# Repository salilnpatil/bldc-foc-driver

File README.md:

# BLDC Field-Oriented Control Driver

A custom three-phase inverter board and closed-loop firmware for driving a brushless DC (BLDC) motor using **Field-Oriented Control (FOC)**. Developed as my final-year B.Tech thesis and deployed as the pitch-axis actuator of a gimbal demonstrator: an external RC-style PWM signal commands a target angle, and the motor tracks it smoothly through a 3:1 gear reduction.

## Stack at a glance

| Layer | Choice |
| --- | --- |
| MCU | STM32G431 (Cortex-M4F + CORDIC coprocessor) |
| Commutation | 6-PWM, voltage-mode FOC ([SimpleFOC](https://simplefoc.com/)) |
| Position sensor | MA730 14-bit magnetic encoder (SPI) |
| Power stage | 3× half-bridge, TI N-channel MOSFETs |
| Setpoint input | RC-style PWM (timer input capture) |
| PCB tool | Autodesk EagleCAD |
| Bus voltage | 12 V (nominal) |

## Visuals

| PCB layout | Wiring diagram |
| --- | --- |
|  |  |

Communication interface:

## Repository layout

```
.
├── Assets/                              Demo GIF, connection diagrams, PCB render, final paper
├── Hardware_assets/
│   ├── Design_FIle(EagleCad)/           EagleCAD .brd + .sch sources
│   ├── Schematic/                       Exported PDF schematic
│   ├── Gerber_file/                     Fabrication-ready Gerbers (.zip)
│   └── BOM_&_Component_selection/       MOSFET trade-off spreadsheet
├── Firmware/
│   └── bldc-doc-driver/                 Arduino sketch (SimpleFOC on STM32G4)
└── README.md
```

## Hardware design

The board is a three-phase inverter built around three half-bridges of TI N-channel power MOSFETs, with an MA730 magnetic encoder front-end and a PWM-input pin exposed to an off-board receiver. A mechanical limit switch on the pitch axis provides a repeatable zero for homing.

**MOSFET selection** — the workbook in `Hardware_assets/BOM_&_Component_selection/` compares two TI candidates evaluated for the low-side/high-side switches:

| Part | Vds | Id | Rds(on) max | Qg | Notes |
| --- | --- | --- | --- | --- | --- |
| `CSD18510Q5B` | 40 V | 42 A | 1.2 mΩ | 118 nC | Lower Qgd, lower voltage headroom |
| `CSD18536KCS` | 60 V | 200 A | 1.3 mΩ | 108 nC | Higher Vds margin, much higher current rating |

Both sit at roughly 1.2–1.3 mΩ Rds(on), so the choice comes down to voltage headroom above the 12 V bus and thermal budget rather than conduction loss.

**Design artefacts**

- EagleCAD sources — [`Hardware_assets/Design_FIle(EagleCad)/Layout_Design_File.sch`](Hardware_assets/Design_FIle(EagleCad)/Layout_Design_File.sch), [`Schematic_Design_File.brd`](Hardware_assets/Design_FIle(EagleCad)/Schematic_Design_File.brd)
- Schematic PDF — [`Hardware_assets/Schematic/Final_Schematic.pdf`](Hardware_assets/Schematic/Final_Schematic.pdf)
- Gerbers — [`Hardware_assets/Gerber_file/Final_Gerber_File.zip`](Hardware_assets/Gerber_file/Final_Gerber_File.zip)

## Firmware

Sketch: [`Firmware/bldc-doc-driver/bldc-doc-driver.ino`](Firmware/bldc-doc-driver/bldc-doc-driver.ino).

**Control law** — SimpleFOC angle-control cascade: `angle (P) → velocity (PI) → q-axis voltage`. Torque mode is `TorqueControlType::voltage`, pole pairs are set to 7, and the motor voltage limit is clamped to `V_PSU / 2` for headroom.

**Parameters** (from the sketch)

| Define / field | Value |
| --- | --- |
| `V_PSU`, `V_LIMIT` | 12.0 V |
| `GEAR_REDUCTION` | 3 (pitch axis) |
| `ACCESSIBLE_ANGLE` | 3.00 rad of mechanical pitch travel |
| `PWM_IN_MIN` / `PWM_IN_MAX` | 4.94 % / 10.06 % duty (≈1.0–2.0 ms pulses) |
| `PID_velocity` P / I / D | 0.2 / 4 / 0 |
| `P_angle.P` | 10 |
| `velocity_limit` | 50 rad/s |

**Startup sequence**

1. Bring up the debug serial (`Serial3`, 115200), the STM32G4 CORDIC unit, the PWM input capture, and the MA730 sensor.
2. Configure driver + motor, run SimpleFOC `initFOC()` electrical alignment.
3. **Homing** — drive the motor slowly toward the limit switch; when it trips, snapshot the encoder angle as `max_angle`, compute `min_angle = max_angle − (ACCESSIBLE_ANGLE × GEAR_REDUCTION)`.
4. Build a linear mapper from input PWM duty `[4.94 %, 10.06 %]` onto `[min_angle, max_angle]`.

**Main loop** — `motor.loopFOC()` runs the current/voltage inner loop; each iteration the PWM-input duty is sampled, mapped to a target angle, clamped to the calibrated travel, and passed to `motor.move(target_angle)`.

### Library dependencies

- [SimpleFOC](https://github.com/simplefoc/Arduino-FOC) — `BLDCMotor`, `BLDCDriver6PWM`
- [SimpleFOC Drivers](https://github.com/simplefoc/Arduino-FOC-drivers) — `MagneticSensorMA730`, `STM32PWMInput`, `STM32G4CORDICTrigFunctions`, `STM32FlashSettingsStorage`
- [Arduino core for STM32 (stm32duino)](https://github.com/stm32duino/Arduino_Core_STM32) — board target: **Generic STM32G4 series / STM32G431xx**

### Build & flash (Arduino IDE)

1. Install Arduino IDE 2.x and the **STM32** boards package following stm32duino's instructions.
2. From Library Manager, install `SimpleFOC` and `SimpleFOC Drivers`.
3. Open `Firmware/bldc-doc-driver/bldc-doc-driver.ino`.
4. Board → *Generic STM32G4 series*; part → *STM32G431xx*; upload method → *STM32CubeProgrammer (SWD)* via an ST-Link.
5. Compile and flash.

### Known gaps / roadmap

- **STM32CubeIDE port** — planned. A HAL/LL implementation in STM32CubeIDE (native 6-PWM timer configuration, ADC-based phase current sensing, CORDIC-accelerated Park/Clarke) is on the roadmap as a production-grade replacement for the Arduino prototype. Not yet in-tree.

## Research paper

Full write-up covering FOC theory, hardware design rationale, and results: [`Assets/Final_Paper.pdf`](Assets/Final_Paper.pdf).

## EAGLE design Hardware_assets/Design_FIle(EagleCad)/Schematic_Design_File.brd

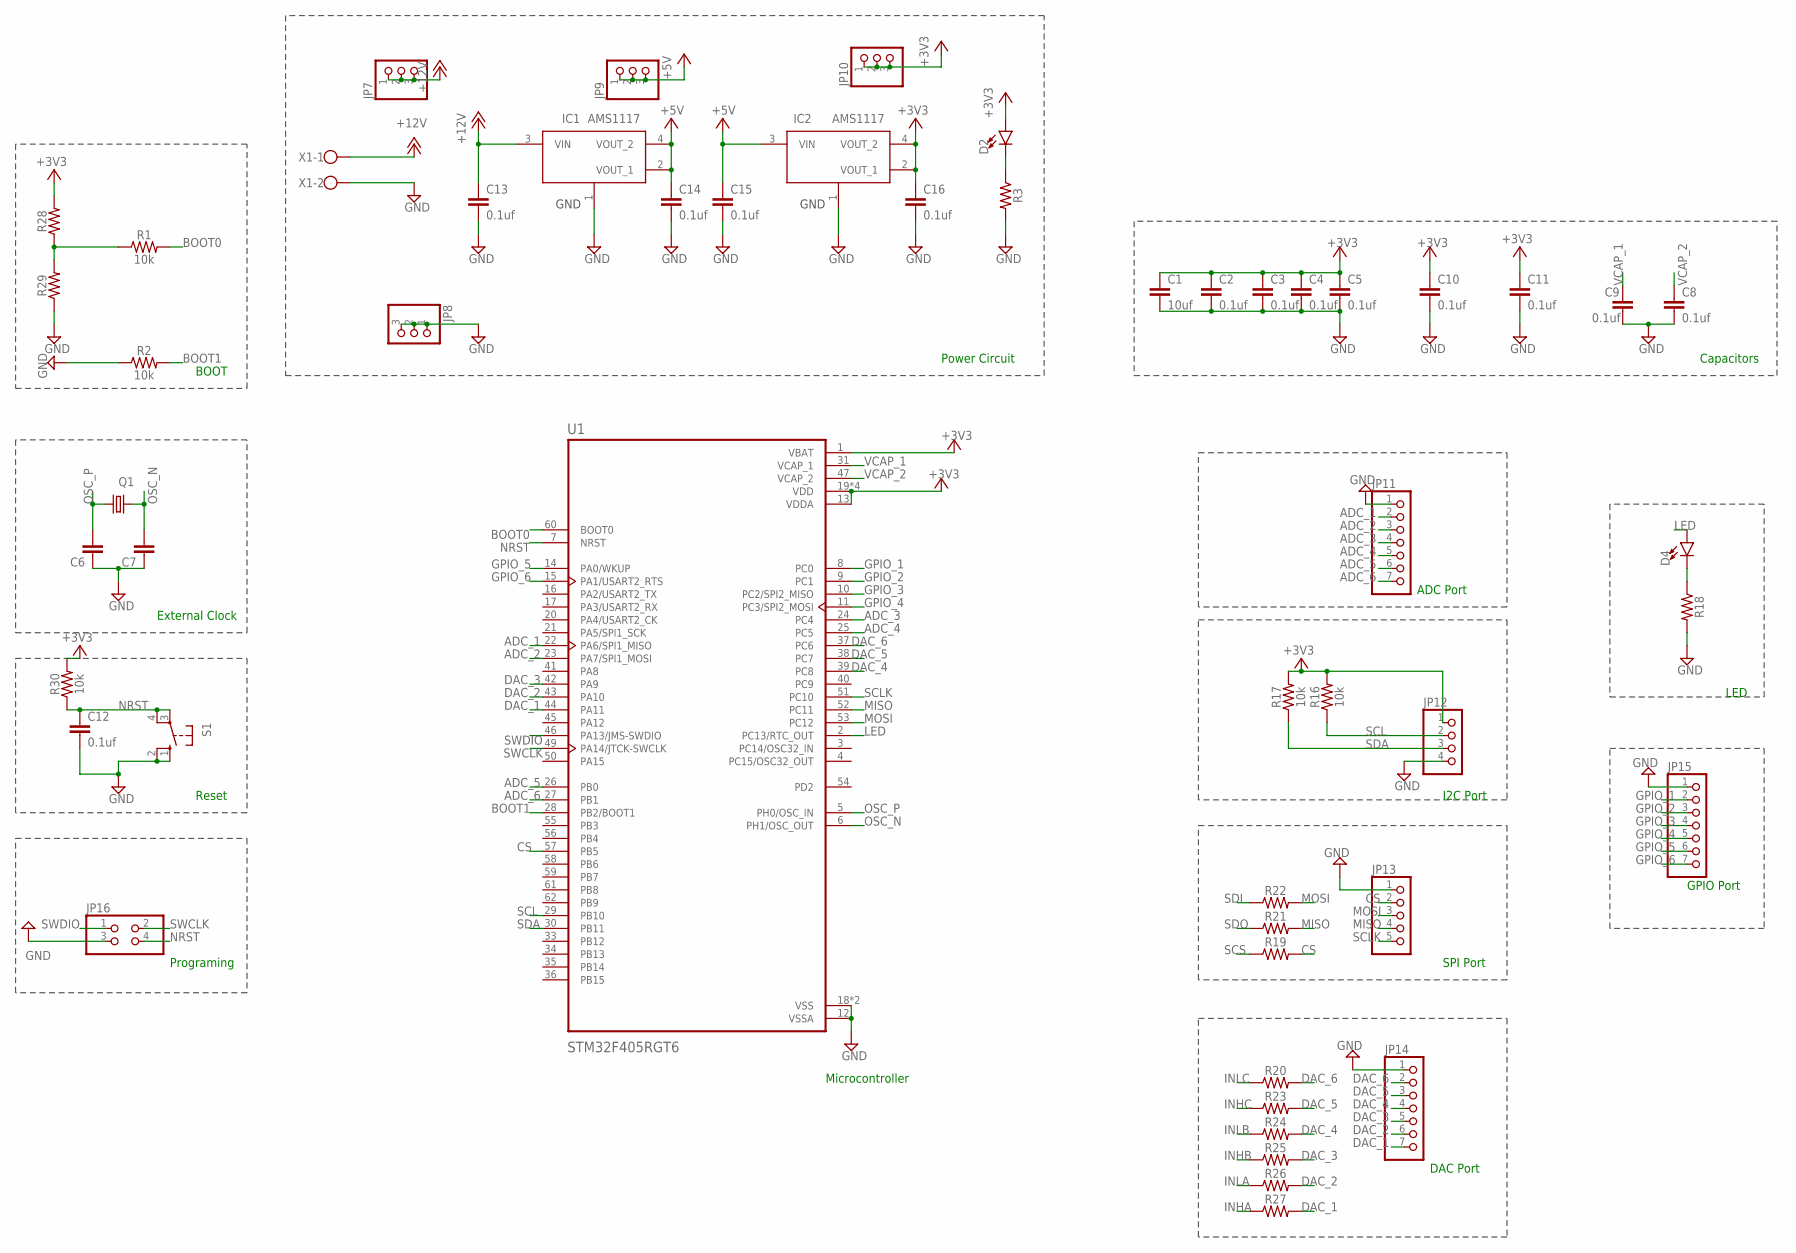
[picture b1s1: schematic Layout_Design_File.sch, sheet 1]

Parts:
C1: 10uf; 0603
C2, C3, C4, C5, C8, C9, C10, C11, C12, C13, C14, C15, C16: 0.1uf; 0603
C6, C7: CAP-0603; 0603
D2, D4: LED1206; LED-1206
IC1, IC2: AMS1117; SOT229P700X180-4N
JP7, JP8, JP9, JP10: PINHD-1X3; 1X03
JP11, JP14, JP15: PINHD-1X7; 1X07
JP12: PINHD-1X4; 1X04
JP13: PINHD-1X5; 1X05
JP16: PINHD-2X2; 2X02
Q1: CRYSTALHC49S; HC49/S
R1, R2, R16, R17, R30: 10k; 0603
R3, R18, R19, R20, R21, R22, R23, R24, R25, R26, R27, R28, R29: 0603
S1: 10-XX; B3F-10XX
U1: STM32F405RGT6; QFP50P1200X1200X160-64N
X1: W237-102

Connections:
+3V3: C1.1, C2.1, C3.1, C4.1, C5.1, C10.1, C11.1, C16.1, D2.A, IC2.2 (VOUT_1), IC2.4 (VOUT_2), JP10.1, JP10.2, JP10.3, JP12.1, R16.2, R17.2, R28.2, R30.2, U1.1 (VBAT), U1.13 (VDDA), U1.19 (VDD), U1.32 (VDD), U1.48 (VDD), U1.64 (VDD); also elsewhere on the board
+5V: C14.1, C15.1, IC1.2 (VOUT_1), IC1.4 (VOUT_2), IC2.3 (VIN), JP9.1, JP9.2, JP9.3
+12V: C13.1, IC1.3 (VIN), JP7.1, JP7.2, JP7.3, X1.1; also elsewhere on the board
ADC_1: JP11.2, U1.22 (PA6/SPI1_MISO)
ADC_2: JP11.3, U1.23 (PA7/SPI1_MOSI)
ADC_3: JP11.4, U1.24 (PC4)
ADC_4: JP11.5, U1.25 (PC5)
ADC_5: JP11.6, U1.26 (PB0)
ADC_6: JP11.7, U1.27 (PB1)
BOOT0: R1.2, U1.60 (BOOT0)
BOOT1: R2.2, U1.28 (PB2/BOOT1)
CS: JP13.2, R19.2, U1.57 (PB5)
DAC_1: JP14.7, R27.2, U1.44 (PA11)
DAC_2: JP14.6, R26.2, U1.43 (PA10)
DAC_3: JP14.5, R25.2, U1.42 (PA9)
DAC_4: JP14.4, R24.2, U1.39 (PC8)
DAC_5: JP14.3, R23.2, U1.38 (PC7)
DAC_6: JP14.2, R20.2, U1.37 (PC6)
GND: C1.2, C2.2, C3.2, C4.2, C5.2, C6.1, C7.1, C8.2, C9.2, C10.2, C11.2, C12.2, C13.2, C14.2, C15.2, C16.2, IC1.1 (GND), IC2.1 (GND), JP8.1, JP8.2, JP8.3, JP11.1, JP12.4, JP13.1, JP14.1, JP15.1, JP16.3, R2.1, R3.2, R18.2, R29.1, S1.1 (S), S1.2 (S1), U1.12 (VSSA), U1.18 (VSS), U1.63 (VSS), X1.2; also elsewhere on the board
GPIO_1: JP15.2, U1.8 (PC0)
GPIO_2: JP15.3, U1.9 (PC1)
GPIO_3: JP15.4, U1.10 (PC2/SPI2_MISO)
GPIO_4: JP15.5, U1.11 (PC3/SPI2_MOSI)
GPIO_5: JP15.6, U1.14 (PA0/WKUP)
GPIO_6: JP15.7, U1.15 (PA1/USART2_RTS)
INHA: R27.1; also elsewhere on the board
INHB: R25.1; also elsewhere on the board
INHC: R23.1; also elsewhere on the board
INLA: R26.1; also elsewhere on the board
INLB: R24.1; also elsewhere on the board
INLC: R20.1; also elsewhere on the board
LED: D4.A, U1.2 (PC13/RTC_OUT)
MISO: JP13.4, R21.2, U1.52 (PC11)
MOSI: JP13.3, R22.2, U1.53 (PC12)
unnamed: D2.C, R3.1
unnamed: D4.C, R18.1
unnamed: R1.1, R28.1, R29.2
NRST: C12.1, JP16.4, R30.1, S1.3, S1.4 (P1), U1.7 (NRST)
OSC_N: C7.2, Q1.2, U1.6 (PH1/OSC_OUT)
OSC_P: C6.2, Q1.1, U1.5 (PH0/OSC_IN)
SCL: JP12.2, R16.1, U1.29 (PB10)
SCLK: JP13.5, U1.51 (PC10); also elsewhere on the board
SCS: R19.1; also elsewhere on the board
SDA: JP12.3, R17.1, U1.30 (PB11)
SDI: R22.1; also elsewhere on the board
SDO: R21.1; also elsewhere on the board
SWCLK: JP16.2, U1.49 (PA14/JTCK-SWCLK)
SWDIO: JP16.1, U1.46 (PA13/JMS-SWDIO)
VCAP_1: C9.1, U1.31 (VCAP_1)
VCAP_2: C8.1, U1.47 (VCAP_2)

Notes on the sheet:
BOOT
External Clock
Reset
Programing
Power Circuit
Capacitors
Microcontroller
ADC Port
I2C Port
SPI Port
DAC Port
GPIO Port
LED

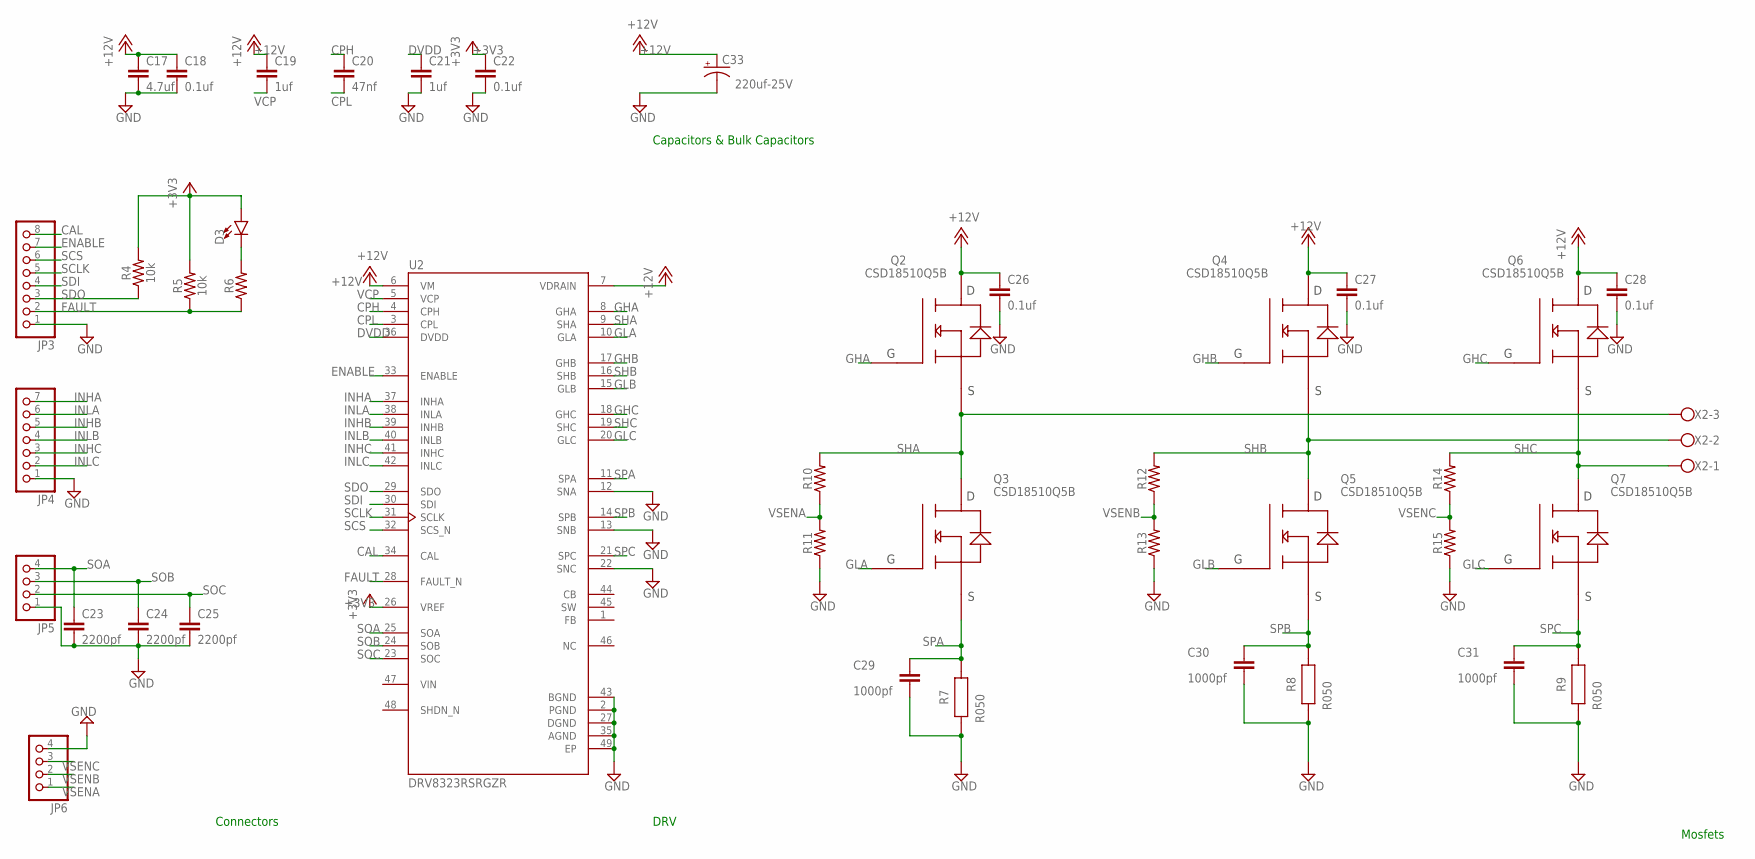
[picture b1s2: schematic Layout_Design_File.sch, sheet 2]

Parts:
C17: 4.7uf; 0603
C18, C22, C26, C27, C28: 0.1uf; 0603
C19, C21: 1uf; 0603
C20: 47nf; 0603
C23, C24, C25: 2200pf; 0603
C29, C30, C31: 1000pf; 0603
C33: 220uf-25V; CPOL-RADIAL-5MM-10MM-NS
D3: LED1206; LED-1206
JP3: PINHD-1X8; 1X08
JP4: PINHD-1X7; 1X07
JP5, JP6: PINHD-1X4; 1X04
Q2, Q3, Q4, Q5, Q6, Q7: CSD18510Q5B; CSD18540Q5BT
R4, R5: 10k; 0603
R6, R10, R11, R12, R13, R14, R15: 0603
R7, R8, R9: R050; WRIS_PSMC_2512_6.3X3.1X0.58X2.2(LXWXHXPW)
U2: DRV8323RSRGZR; QFN50P700X700X100-49N
X2: W237-103

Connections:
+3V3: C22.1, D3.A, R4.2, R5.2, U2.26 (VREF); also elsewhere on the board
+12V: C17.1, C18.1, C19.1, C26.1, C27.1, C28.1, C33.+, Q2.5 (D), Q2.6 (D), Q2.7 (D), Q2.8 (D), Q2.9 (D), Q4.5 (D), Q4.6 (D), Q4.7 (D), Q4.8 (D), Q4.9 (D), Q6.5 (D), Q6.6 (D), Q6.7 (D), Q6.8 (D), Q6.9 (D), U2.6 (VM), U2.7 (VDRAIN); also elsewhere on the board
CAL: JP3.8, U2.34 (CAL)
CB: U2.44 (CB)
CPH: C20.1, U2.4 (CPH)
CPL: C20.2, U2.3 (CPL)
DVDD: C21.1, U2.36 (DVDD)
ENABLE: JP3.7, U2.33 (ENABLE)
FAULT: JP3.2, R5.1, R6.1, U2.28 (FAULT_N)
GHA: Q2.4 (G), U2.8 (GHA)
GHB: Q4.4 (G), U2.17 (GHB)
GHC: Q6.4 (G), U2.18 (GHC)
GLA: Q3.4 (G), U2.10 (GLA)
GLB: Q5.4 (G), U2.15 (GLB)
GLC: Q7.4 (G), U2.20 (GLC)
GND: C17.2, C18.2, C21.2, C22.2, C23.2, C24.2, C25.2, C26.2, C27.2, C28.2, C29.2, C30.2, C31.2, C33.-, JP3.1, JP4.1, JP5.1, JP6.4, R7.1, R8.1, R9.1, R11.1, R13.1, R15.1, U2.2 (PGND), U2.12 (SNA), U2.13 (SNB), U2.22 (SNC), U2.27 (DGND), U2.35 (AGND), U2.43 (BGND), U2.49 (EP); also elsewhere on the board
INHA: JP4.7, U2.37 (INHA); also elsewhere on the board
INHB: JP4.5, U2.39 (INHB); also elsewhere on the board
INHC: JP4.3, U2.41 (INHC); also elsewhere on the board
INLA: JP4.6, U2.38 (INLA); also elsewhere on the board
INLB: JP4.4, U2.40 (INLB); also elsewhere on the board
INLC: JP4.2, U2.42 (INLC); also elsewhere on the board
unnamed: D3.C, R6.2
SCLK: JP3.5, U2.31 (SCLK); also elsewhere on the board
SCS: JP3.6, U2.32 (SCS_N); also elsewhere on the board
SDI: JP3.4, U2.30 (SDI); also elsewhere on the board
SDO: JP3.3, R4.1, U2.29 (SDO); also elsewhere on the board
SHA: Q2.1 (S), Q2.2 (S), Q2.3 (S), Q3.5 (D), Q3.6 (D), Q3.7 (D), Q3.8 (D), Q3.9 (D), R10.2, U2.9 (SHA), X2.3
SHB: Q4.1 (S), Q4.2 (S), Q4.3 (S), Q5.5 (D), Q5.6 (D), Q5.7 (D), Q5.8 (D), Q5.9 (D), R12.2, U2.16 (SHB), X2.2
SHC: Q6.1 (S), Q6.2 (S), Q6.3 (S), Q7.5 (D), Q7.6 (D), Q7.7 (D), Q7.8 (D), Q7.9 (D), R14.2, U2.19 (SHC), X2.1
SOA: C23.1, JP5.4, U2.25 (SOA)
SOB: C24.1, JP5.3, U2.24 (SOB)
SOC: C25.1, JP5.2, U2.23 (SOC)
SPA: C29.1, Q3.1 (S), Q3.2 (S), Q3.3 (S), R7.2, U2.11 (SPA)
SPB: C30.1, Q5.1 (S), Q5.2 (S), Q5.3 (S), R8.2, U2.14 (SPB)
SPC: C31.1, Q7.1 (S), Q7.2 (S), Q7.3 (S), R9.2, U2.21 (SPC)
VCP: C19.2, U2.5 (VCP)
VIN: U2.47 (VIN)
VSENA: JP6.1, R10.1, R11.2
VSENB: JP6.2, R12.1, R13.2
VSENC: JP6.3, R14.1, R15.2

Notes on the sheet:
Capacitors & Bulk Capacitors
Connectors
DRV
Mosfets

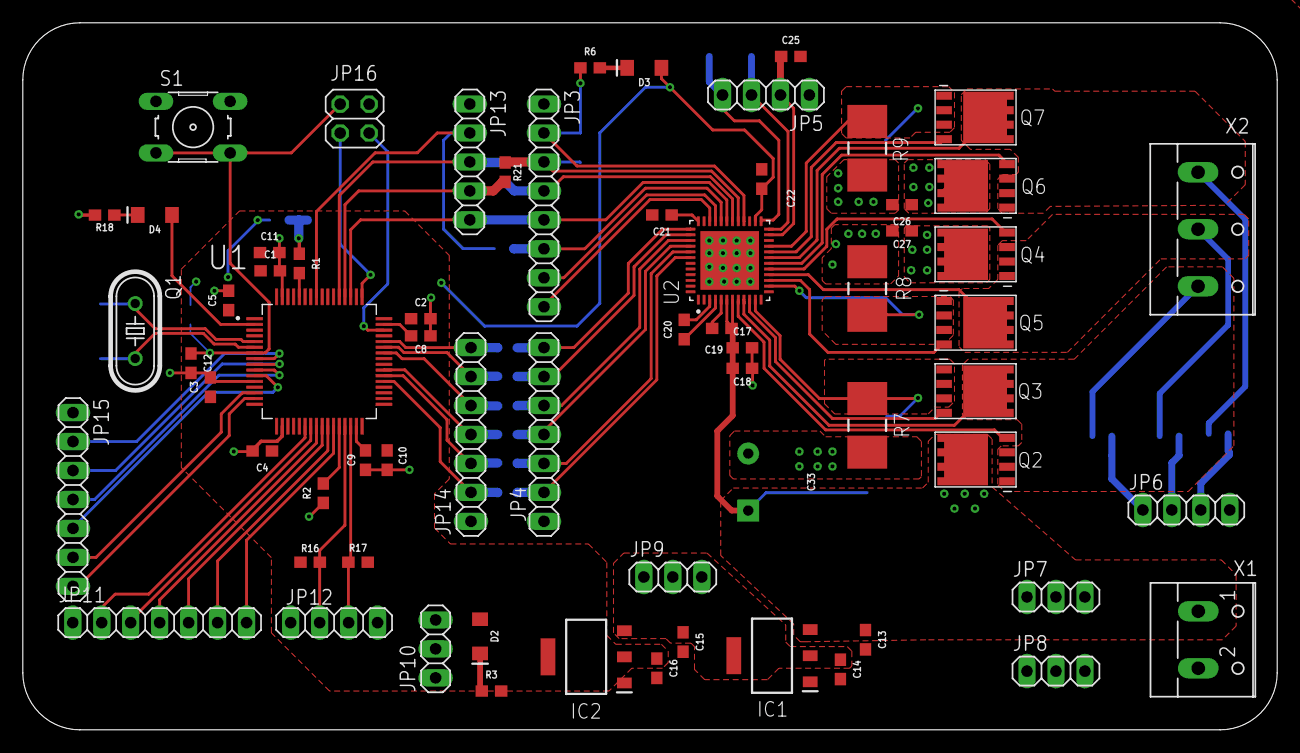
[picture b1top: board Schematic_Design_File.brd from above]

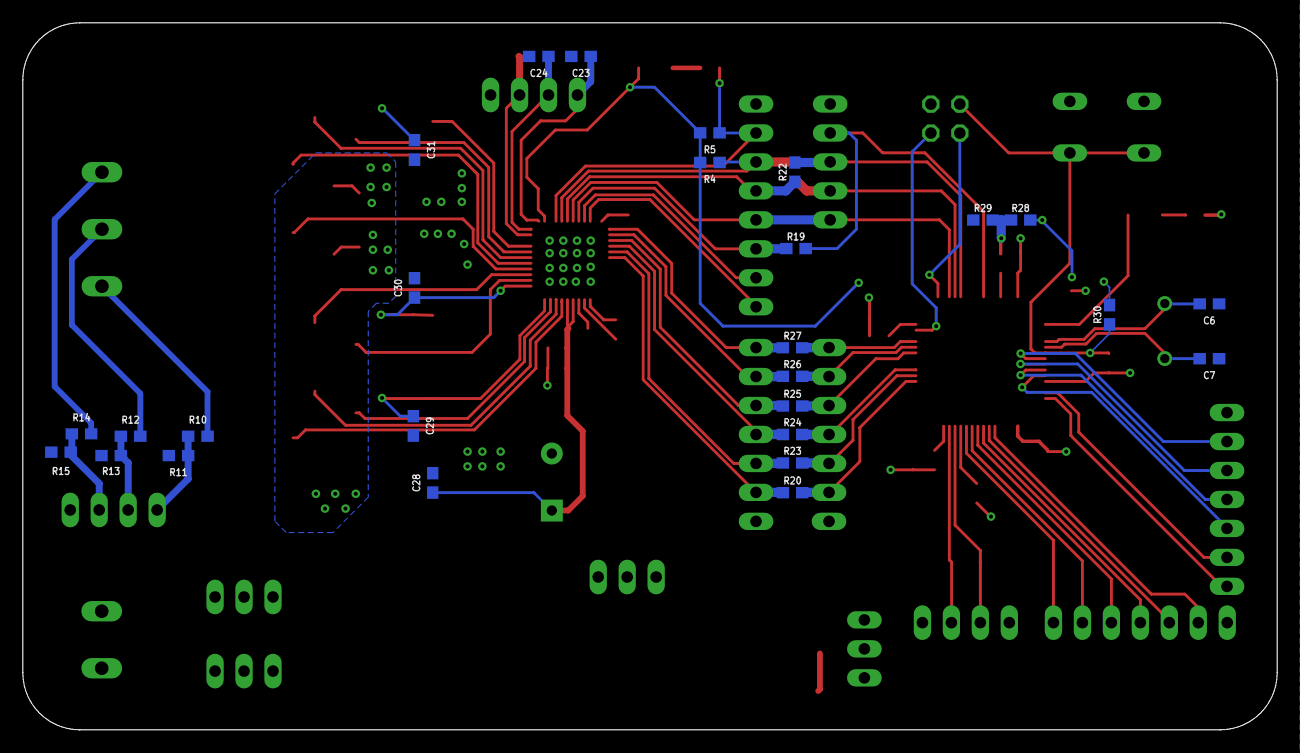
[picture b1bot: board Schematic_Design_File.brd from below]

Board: 2 copper layers, 110.0 x 62.0 mm, 93 parts (27 on the bottom side), 76 nets.

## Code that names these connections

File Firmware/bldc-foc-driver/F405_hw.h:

#ifndef F405_HW_H
#define F405_HW_H

/*
 * F405_hw.h — board pin map for the BLDC FOC driver board (STM32F405RGT6).
 *
 * Values are derived directly from the committed EagleCAD schematic at
 *   Hardware_assets/Design_FIle(EagleCad)/Layout_Design_File.sch
 *
 * Two categories of pins below:
 *
 *   HARDWIRED  — physically routed on the PCB from the MCU to the DRV8323
 *                gate driver through series resistors (R19..R27). These
 *                values are authoritative and should not be changed.
 *
 *   EXTERNAL   — the board brings the DRV8323 control pins (ENABLE, FAULT,
 *                CAL) out on JP3, and spare MCU GPIOs out on JP11..JP15.
 *                The connections from MCU GPIO to DRV-ENABLE, to the MA730
 *                encoder's chip-select, and to the limit switch / PWM
 *                input / debug UART are made off-board with jumper wires
 *                chosen at assembly time. The placeholders below are
 *                *suggested defaults* taken from pins broken out on JP15
 *                (GPIOs) and JP12 (UART-capable).
 *
 *                >>> VERIFY these match your physical jumper wiring before
 *                >>> flashing. A wrong ENABLE pin can leave the DRV8323 in
 *                >>> a permanently enabled state with no software control.
 *
 * Note: the parent sketch also calls into the STM32G4 hardware CORDIC,
 * which does not exist on the F4 family. Those calls must be removed for
 * the F405 target. This header only defines pins; it does not fix that.
 */

// ---------------------------------------------------------------------------
// HARDWIRED — 6-PWM gate-driver inputs to DRV8323RS (via R20/R23..R27)
// ---------------------------------------------------------------------------
// Phase A:  PA11 (R27) -> INHA,  PA10 (R26) -> INLA
// Phase B:  PA9  (R25) -> INHB,  PC8  (R24) -> INLB
// Phase C:  PC7  (R23) -> INHC,  PC6  (R20) -> INLC
//
// Timer caveat: these 6 pins span TIM1 CH2/CH3/CH4 (PA9/PA10/PA11) and
// TIM3/TIM8 CH1/CH2/CH3 (PC6/PC7/PC8). PA11 is TIM1_CH4 which has no
// complementary output on the F4, and phase B's high-side (PA9) and
// low-side (PC8) sit on different timers. SimpleFOC's BLDCDriver6PWM will
// therefore fall back to independent-channel PWM with software dead-time.
// Confirm phasing and dead-time on a scope during bring-up.
#define MOT1_OUT_H  PA11
#define MOT1_OUT_L  PA10
#define MOT2_OUT_H  PA9
#define MOT2_OUT_L  PC8
#define MOT3_OUT_H  PC7
#define MOT3_OUT_L  PC6

// ---------------------------------------------------------------------------
// HARDWIRED — SPI bus from MCU to DRV8323RS (via R19/R21/R22)
// ---------------------------------------------------------------------------
// PC10 -> SCLK, PC11 -> MISO (R21 -> DRV SDO), PC12 -> MOSI (R22 -> DRV SDI),
// PB5  -> CS   (R19 -> DRV SCS_N). This SPI is used only for DRV8323
// configuration and is not exercised by the current sketch.
#define DRV8323_CS  PB5

// ---------------------------------------------------------------------------
// EXTERNAL — jumper-wired via headers. Verify against your board.
// ---------------------------------------------------------------------------

// MA730 magnetic encoder chip-select. The MA730 shares the MCU SPI bus
// (SCLK=PC10, MISO=PC11, MOSI=PC12) with the DRV8323; only CS is unique.
// Available GPIOs on JP15: PC0, PC1, PC2, PC3, PA0, PA1.
// Default: PC0 (JP15 pin 2).
#define SENSOR1_CS  PC0

// DRV8323 master ENABLE. Jumper JP3 pin 7 to an MCU GPIO.
// Default: PC1 (JP15 pin 3).
#define ENABLE      PC1

// Homing limit switch (sketch enables INPUT_PULLUP).
// Default: PC2 (JP15 pin 4).
#define LIMIT_SW    PC2

// External RC-style PWM setpoint input. Must land on a pin that maps to a
// timer input-capture channel in the stm32duino core.
// Default: PA0 (JP15 pin 6) — TIM2_CH1 / TIM5_CH1 on STM32F405.
#define PWM_IN2     PA0

// Debug UART (SimpleFOC monitor / println). On STM32F405, USART3 is
// available on PB10 (TX) / PB11 (RX), both broken out on JP12. The I2C
// pull-ups R16/R17 on these nets do not interfere with UART operation.
#define PIN_SERIAL_TX  PB10
#define PIN_SERIAL_RX  PB11

#endif // F405_HW_H

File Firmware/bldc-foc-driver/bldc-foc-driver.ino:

#include <SimpleFOC.h>
#define MOT1_OUT_H PA8
#define MOT2_OUT_H PA9
#define MOT3_OUT_H PA10
#define MOT1_OUT_L PA7 // PA7     //PC13
#define MOT2_OUT_L   PB0       //PA12
#define MOT3_OUT_L   PB1     //PB1       //PB15
// Motor instance
MagneticSensorI2C sensor1 = MagneticSensorI2C(AS5600_I2C);

// example of stm32 defining 2nd bus
// TwoWire Wire1(PB11, PB10);
BLDCMotor motor = BLDCMotor(7);
BLDCDriver6PWM driver = BLDCDriver6PWM(MOT1_OUT_H, MOT1_OUT_L, MOT2_OUT_H, MOT2_OUT_L, MOT3_OUT_H, MOT3_OUT_L);
// BLDCDriver6PWM driver = BLDCDriver6PWM(8, 28, 9, 29, 10, 30, 27);
// LowsideCurrentSense currentSense = LowsideCurrentSense(0.003f, -64.0f/7.0f, A_OP1_OUT, A_OP2_OUT, A_OP3_OUT);


// encoder instance 


//Encoder encoder = Encoder(A_HALL2, A_HALL3, 2048, A_HALL1);

// // Interrupt routine intialisation
// // channel A and B callbacks
// void doA(){encoder.handleA();}
// void doB(){encoder.handleB();}
// void doIndex(){encoder.handleIndex();}

// instantiate the commander
// Commander command = Commander(Serial);
// void doTarget(char* cmd) { command.motion(&motor, cmd); }

void setup() {
  
  // // initialize encoder sensor hardware
  // encoder.init();
  // encoder.enableInterrupts(doA, doB); 
  sensor1.init();
  // // link the motor to the sensor
  motor.linkSensor(&sensor1);
  
  // driver config
  // power supply voltage [V]
  driver.voltage_power_supply = 12;
  driver.init();
  // link the motor and the driver
  motor.linkDriver(&driver);
 

  // aligning voltage [V]
  motor.voltage_sensor_align = 3;
  // index search velocity [rad/s]
  motor.velocity_index_search = 3;

  // set motion control loop to be used
    motor.foc_modulation = FOCModulationType::SpaceVectorPWM;
  motor.controller = MotionControlType::velocity_openloop;

  // contoller configuration 
  // default parameters in defaults.h

  // velocity PI controller parameters
  motor.PID_velocity.P = 0.2;
  motor.PID_velocity.I = 20;
  // default voltage_power_supply
  motor.voltage_limit = 6;
  // jerk control using voltage voltage ramp
  // default value is 300 volts per sec  ~ 0.3V per millisecond
  motor.PID_velocity.output_ramp = 1000;
 
  // velocity low pass filtering time constant
  motor.LPF_velocity.Tf = 0.01;

  // angle P controller
  motor.P_angle.P = 20;
  //  maximal velocity of the position control
  motor.velocity_limit = 10;


  // use monitoring with serial 
  // Serial.begin(115200);
  // comment out if not needed
  // motor.useMonitoring(Serial);
  
  // initialize motor
  motor.init();
  // align encoder and start FOC
  motor.initFOC();


  // Serial.println(F("Motor ready."));
  // Serial.println(F("Set the target angle using serial terminal:"));
  _delay(1000);
}

void loop() {

  
  // main FOC algorithm function
  motor.loopFOC();

  // Motion control function
  motor.move(5);


}

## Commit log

2026-04-21 added hardware files
2026-04-22 added all the the assets
2026-04-22 changed demo vid to git and add doc
2026-04-22 edited readme and add firmware
2026-04-23 changed readme
2026-04-23 uploaded correct versio of firmware

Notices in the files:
parts and their libraries:
SparkFun-Capacitors: Licensing: Creative Commons ShareAlike 4.0 International - https://creativecommons.org/licenses/by-sa/4.0
Wurth_Resistor_WRIS-PSMC: Copyright: Würth Elektronik
